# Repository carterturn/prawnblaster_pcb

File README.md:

Prawnblaster PCB
================

Provides nice panel-mountable BNC connections and ground-isolated USB
for the Prawnblaster (<https://github.com/labscript-suite/prawnblaster>).

Loosely based on <https://github.com/TU-Darmstadt-APQ/Prawnblaster_Breakout>.

-Trigger input is buffered to allow 5V input without risk to Pi Pico.

-Output clocklines are buffered to drive at 5V (and avoid damage to Pi Pico from those lines floating to 5V).

-Clock input is buffered.

-Analog ADuM5000 used for 5V power isolation and Analog ADuM4160 used for USB isolation. Note that speed is fixed at high speed.

-Fits in 1U Bud box (slightly too tall, so upper panel bends slightly, but probably fine).

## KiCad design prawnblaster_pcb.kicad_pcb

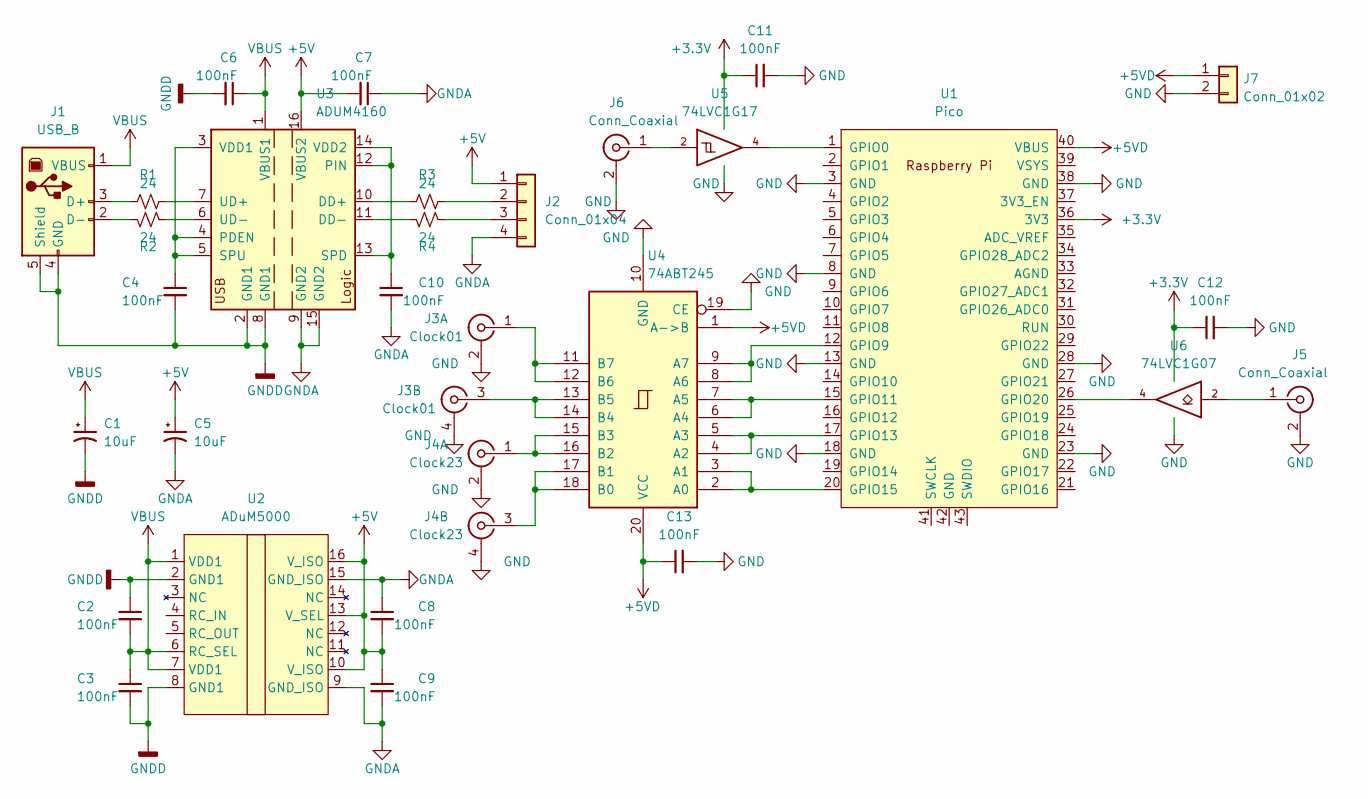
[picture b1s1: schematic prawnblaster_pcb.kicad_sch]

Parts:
C1, C5: 10uF; CP_Radial_D5.0mm_P2.00mm
C2, C3, C4, C6, C7, C8, C9, C10, C11, C12, C13: 100nF; C_0805_2012Metric
J1: USB_B; USB_B_OST_USB-B1HSxx_Horizontal
J2: Conn_01x04; PinHeader_1x04_P2.54mm_Vertical
J3: Clock01; BNC_Amphenol_031-6575_Horizontal
J4: Clock23; BNC_Amphenol_031-6575_Horizontal
J5, J6: Conn_Coaxial; BNC_Amphenol_B6252HB-NPP3G-50_Horizontal
J7: Conn_01x02; PinHeader_1x02_P2.54mm_Vertical
R1, R2, R3, R4: 24; R_0805_2012Metric
U1: Pico; RPi_Pico_SMD_TH
U2: ADuM5000; SOIC-16W_7.5x10.3mm_P1.27mm
U3: ADUM4160; SOIC-16W_7.5x10.3mm_P1.27mm
U4: 74ABT245; SOIC-20W_7.5x12.8mm_P1.27mm
U5: 74LVC1G17; SOT-23-5_HandSoldering
U6: 74LVC1G07; SOT-23-5_HandSoldering

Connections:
+3.3V: C11.1, C12.1, U1.36 (3V3), U5.5 (VCC), U6.5 (VCC)
+5V: C5.1, C7.2, C8.2, C9.1, J2.1, U2.10 (V_ISO), U2.13 (V_SEL), U2.16 (V_ISO), U3.16 (VBUS2)
+5VD: C13.1, J7.1, U1.40 (VBUS), U4.1 (A->B), U4.20 (VCC)
GND: C11.2, C12.2, C13.2, J3.2 (Ext1), J3.4 (Ext2), J4.2 (Ext1), J4.4 (Ext2), J5.2 (Ext), J6.2 (Ext), J7.2, U1.3 (GND), U1.8 (GND), U1.13 (GND), U1.18 (GND), U1.23 (GND), U1.28 (GND), U1.38 (GND), U4.10 (GND), U4.19 (CE), U5.3 (GND), U6.3 (GND)
GNDA: C5.2, C7.1, C8.1, C9.2, C10.2, J2.4, U2.9 (GND_ISO), U2.15 (GND_ISO), U3.9 (GND2), U3.15 (GND2)
GNDD: C1.2, C2.1, C3.2, C4.2, C6.2, J1.4 (GND), J1.5 (Shield), U2.2 (GND1), U2.8 (GND1), U3.2 (GND1), U3.8 (GND1)
unnamed: C4.1, U3.3 (VDD1), U3.4 (PDEN), U3.5 (SPU)
unnamed: C10.1, U3.12 (PIN), U3.13 (SPD), U3.14 (VDD2)
unnamed: J1.2 (D-), R2.1
unnamed: J1.3 (D+), R1.1
unnamed: J2.2, R3.2
unnamed: J2.3, R4.2
unnamed: J5.1 (In), U6.2
unnamed: J6.1 (In), U5.2
unnamed: R1.2, U3.7 (UD+)
unnamed: R2.2, U3.6 (UD-)
unnamed: R3.1, U3.10 (DD+)
unnamed: R4.1, U3.11 (DD-)
unnamed: U1.1 (GPIO0), U5.4
unnamed: U1.12 (GPIO9), U4.8 (A6), U4.9 (A7)
unnamed: U1.15 (GPIO11), U4.6 (A4), U4.7 (A5)
unnamed: U1.17 (GPIO13), U4.4 (A2), U4.5 (A3)
unnamed: U1.20 (GPIO15), U4.2 (A0), U4.3 (A1)
unnamed: U1.26 (GPIO20), U6.4
unnamed: J3.1 (In1), U4.11 (B7), U4.12 (B6)
unnamed: J3.3 (In2), U4.13 (B5), U4.14 (B4)
unnamed: J4.1 (In1), U4.15 (B3), U4.16 (B2)
unnamed: J4.3 (In2), U4.17 (B1), U4.18 (B0)
VBUS: C1.1, C2.2, C3.1, C6.1, J1.1 (VBUS), U2.1 (VDD1), U2.6 (RC_SEL), U2.7 (VDD1), U3.1 (VBUS1)

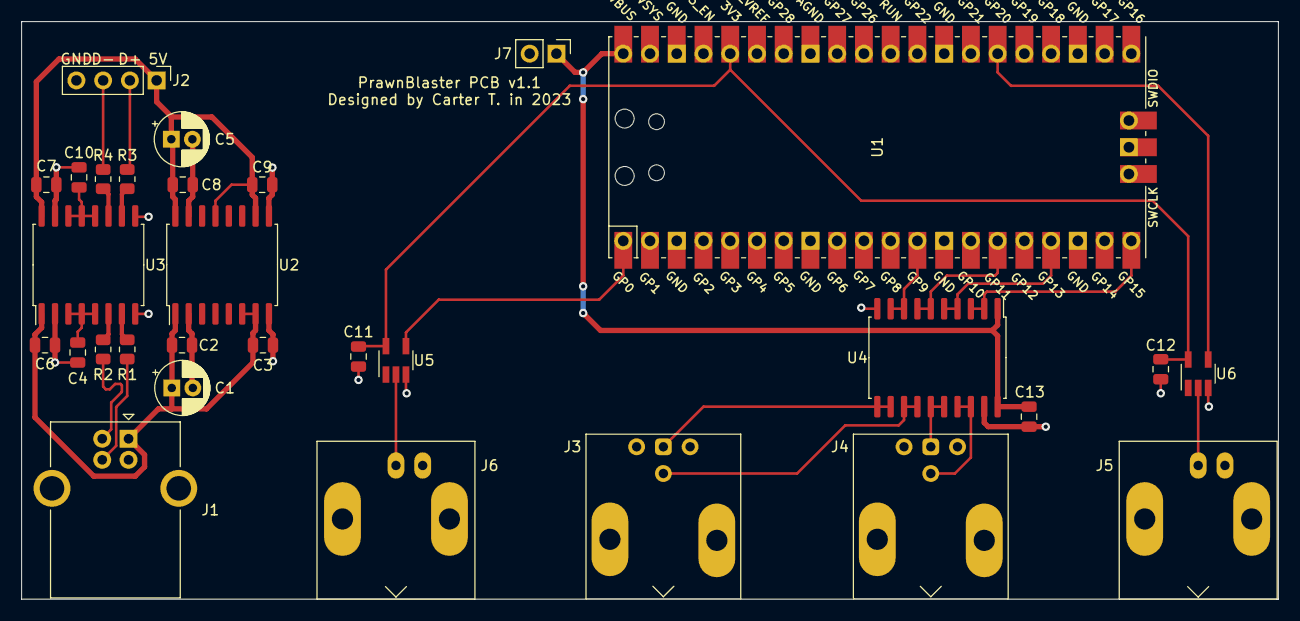
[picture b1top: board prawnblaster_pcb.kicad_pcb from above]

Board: 2 copper layers, 119.4 x 54.9 mm, 30 parts (0 on the bottom side), 29 nets.

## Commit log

2023-02-02 Initial commit, manufactured as v1.
    USB isolation and trigger output work
2023-02-02 Fixed trigger plug wiring
2023-02-02 Updated version number. Now 1.1
2023-03-19 Exported step file
2023-03-19 Adding README
